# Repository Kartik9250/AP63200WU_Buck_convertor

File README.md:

# Variable Buck Converter — KiCad PCB

A variable output synchronous buck converter designed as a practice PCB in KiCad. Takes a USB-C input and delivers a tunable regulated output over USB-A and screw terminals.

---

## Specs

| Parameter | Value |
|---|---|
| Input voltage (Vin) | 0.8V – 12V |
| Output voltage (Vout) | 0.8V – Vin (adjustable) |
| Max output current | 2A |
| Controller IC | AP63200WU (synchronous buck) |
| Input connector | USB-C (power only) |
| Output connector | USB-A + screw terminal |

---

## How it works

The AP63200WU is a synchronous buck regulator. It switches an internal MOSFET at high frequency, and the inductor + output capacitors smooth that into a steady DC output.

Output voltage is set by a resistor divider on the feedback (FB) pin:

```
Vout = 0.8V × (1 + RV1/R1)
```

- **RV1** — 10kΩ trimmer pot (wiper on FB, adjusts output)
- **R1** — 750Ω fixed resistor (sets lower bound)

Turning the pot changes the divider ratio, which changes Vout. The IC regulates to keep FB at 0.8V (internal reference).

---

## Schematic overview

```
USB-C (J1) ──► VAA ──► U1 (AP63200WU) ──► L1 (2.2µH) ──► Vout
                         │                                    │
                        C1                          C2, C3, C4, C5, RV1, R1
                      (10µF)               (snubber, bulk caps, feedback divider)

Vout ──► USB-A (J4)
Vout ──► Screw terminal (J3)
VAA  ──► Screw terminal (J2)
```

---

## Key design decisions

- **Snubber cap (C2 — 100nF, C3 — 100pF on SW node)** — damps ringing on the switching node, reduces EMI
- **Dual 22µF output caps (C4, C5)** — bulk capacitance for low output ripple
- **10µF input cap (C1)** — decouples the input supply
- **USB-C power-only footprint** — CC pins left unconnected (no PD negotiation, passive 5V input assumed)
- **Feedback net (Net-U1-FB) kept short** — sensitive node, routed away from the SW node to avoid noise coupling

---

## Project files

| File | Description |
|---|---|
| `buck_convertor.kicad_pro` | KiCad project file |
| `buck_convertor.kicad_sch` | Schematic |
| `buck_convertor.kicad_pcb` | PCB layout |
| `buck_convertor.kicad_prl` | Local project settings |

---

## Images

| Schematic | PCB Routing | 3D Render |
|---|---|---|
|  |  |  |

---

## Tools used

- [KiCad 9.0](https://www.kicad.org/) — schematic capture & PCB layout

---

## Status

Practice / draft — not manufactured or tested. Layout is functional but not optimised for production (ground plane, thermal relief, DRC cleanup still pending).

---

## License

MIT — feel free to use, fork, or build on this.

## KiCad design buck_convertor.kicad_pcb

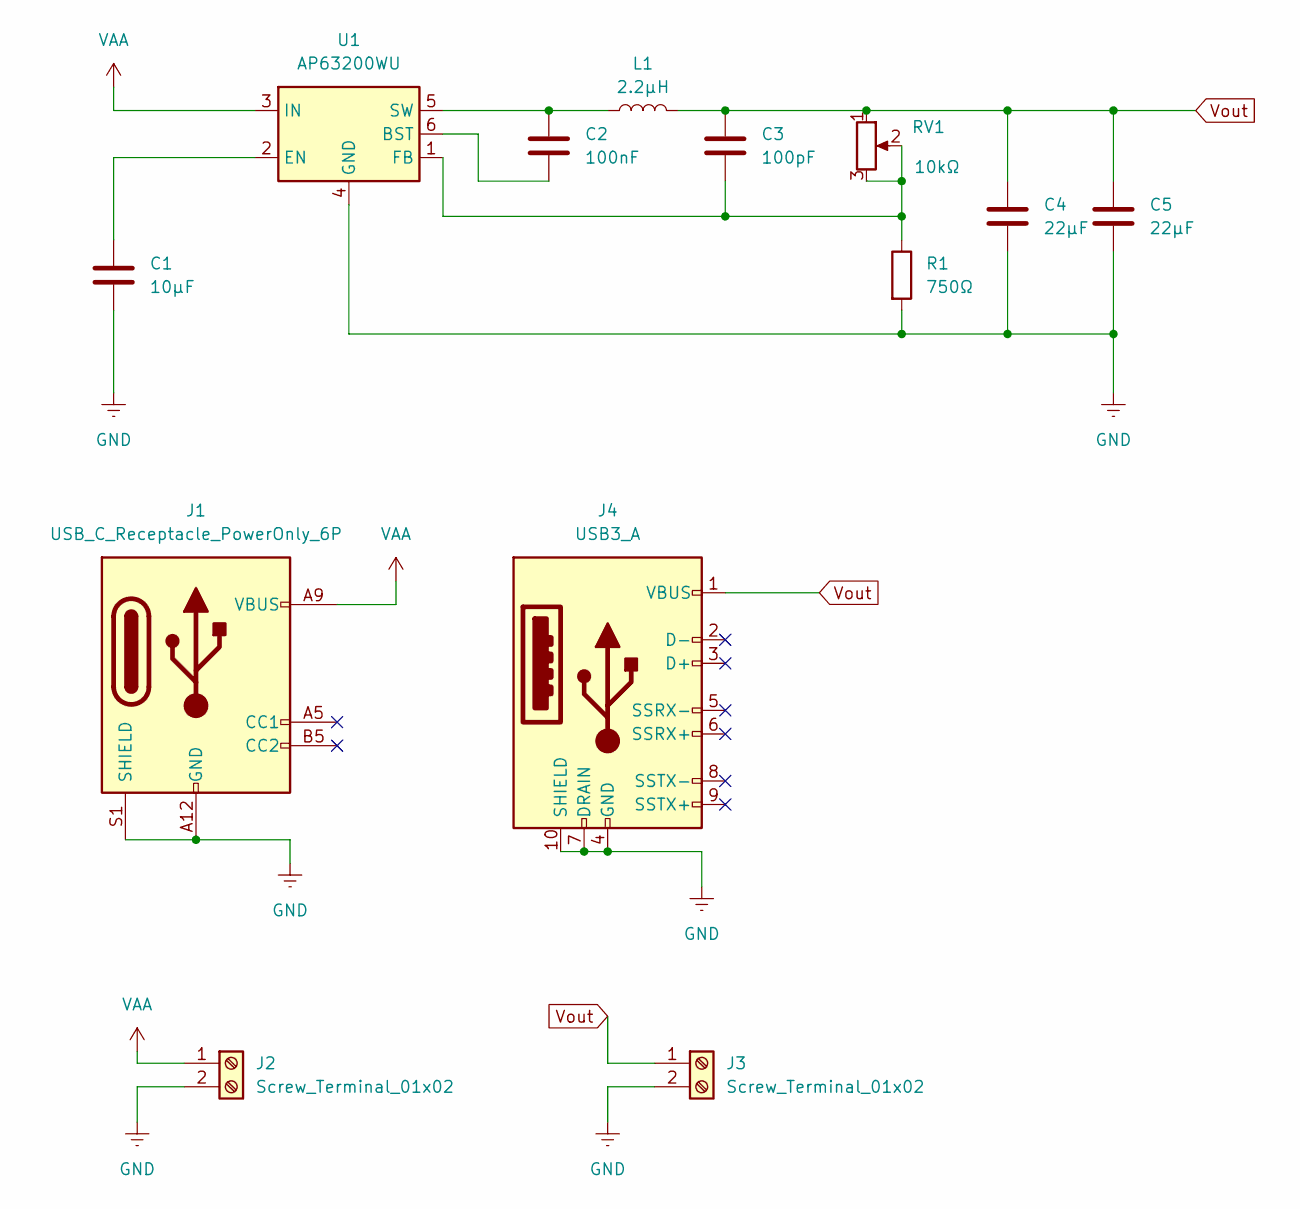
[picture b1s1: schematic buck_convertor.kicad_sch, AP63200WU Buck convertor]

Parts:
C1: 10μF; C_0805_2012Metric_Pad1.18x1.45mm_HandSolder
C2: 100nF; C_0805_2012Metric_Pad1.18x1.45mm_HandSolder
C3: 100pF; C_0805_2012Metric_Pad1.18x1.45mm_HandSolder
C4, C5: 22μF; C_0805_2012Metric_Pad1.18x1.45mm_HandSolder
J1: USB_C_Receptacle_PowerOnly_6P; USB_C_Receptacle_GCT_USB4125-xx-x_6P_TopMnt_Horizontal
J2, J3: Screw_Terminal_01x02; TerminalBlock_Xinya_XY308-2.54-2P_1x02_P2.54mm_Horizontal
J4: USB3_A; USB3_A_Receptacle_Wuerth_692122030100
L1: 2.2μH; L_0805_2012Metric_Pad1.05x1.20mm_HandSolder
R1: 750Ω; R_0805_2012Metric_Pad1.20x1.40mm_HandSolder
RV1: 10kΩ; Potentiometer_Bourns_3224W_Vertical
U1: AP63200WU; TSOT-23-6

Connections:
GND: C1.2, C4.2, C5.2, J1.A12 (GND), J1.B12 (GND), J1.S1 (SHIELD), J2.2, J3.2, J4.4 (GND), J4.7 (DRAIN), J4.10 (SHIELD), R1.2, U1.4 (GND)
unnamed: C2.2, U1.6 (BST)
unnamed: C1.1, U1.2 (EN)
unnamed: C3.2, R1.1, RV1.2, RV1.3, U1.1 (FB)
unnamed: C2.1, L1.1, U1.5 (SW)
VAA: J1.A9 (VBUS), J1.B9 (VBUS), J2.1, U1.3 (IN)
Vout: C3.1, C4.1, C5.1, J3.1, J4.1 (VBUS), L1.2, RV1.1

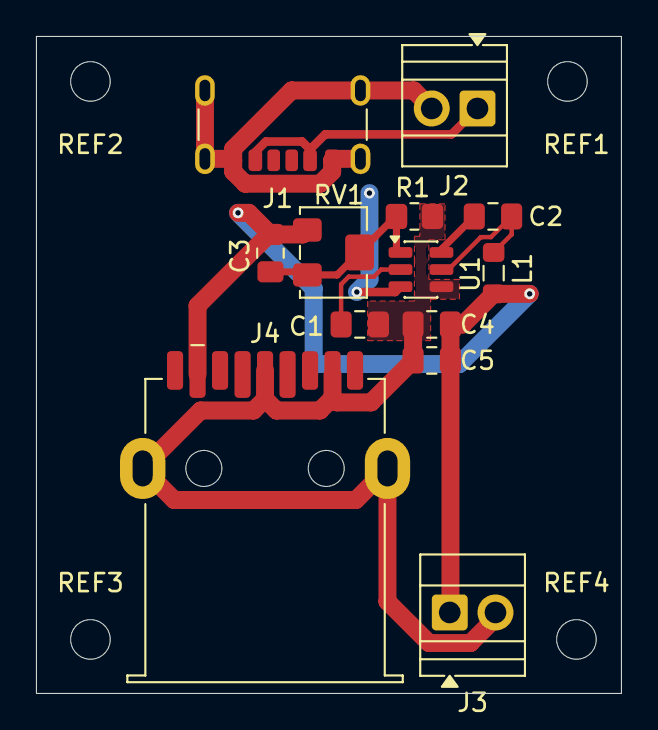
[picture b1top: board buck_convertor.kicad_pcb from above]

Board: 2 copper layers, 32.5 x 36.5 mm, 17 parts (0 on the bottom side), 7 nets.

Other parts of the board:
REF1, REF2, REF3, REF4: MountingHole_2.2mm_M2

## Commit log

2026-04-29 Added pcb schematic
2026-04-29 Added pcb layout design
2026-04-29 Added additional .pro and .prl files
2026-04-29 Updated readme
    - Added project description
    - Added Specs
    - Overiew of PCB working
2026-04-29 Added images for schematic, routing, 3d render
2026-04-29 Added MIT License
